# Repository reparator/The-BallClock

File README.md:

# The-BallClock
A minimalistic Clock

If you want to build one or if you are interested in the project, here you can find the parts and instructions:

https://www.thingiverse.com/thing:5811567

https://www.instructables.com/The-BallClock

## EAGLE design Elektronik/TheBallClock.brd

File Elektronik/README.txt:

The BallClock:
Here you find all files related to the electronics hardware: 
Schematics, board, BOM, layouts, assembly diagrams

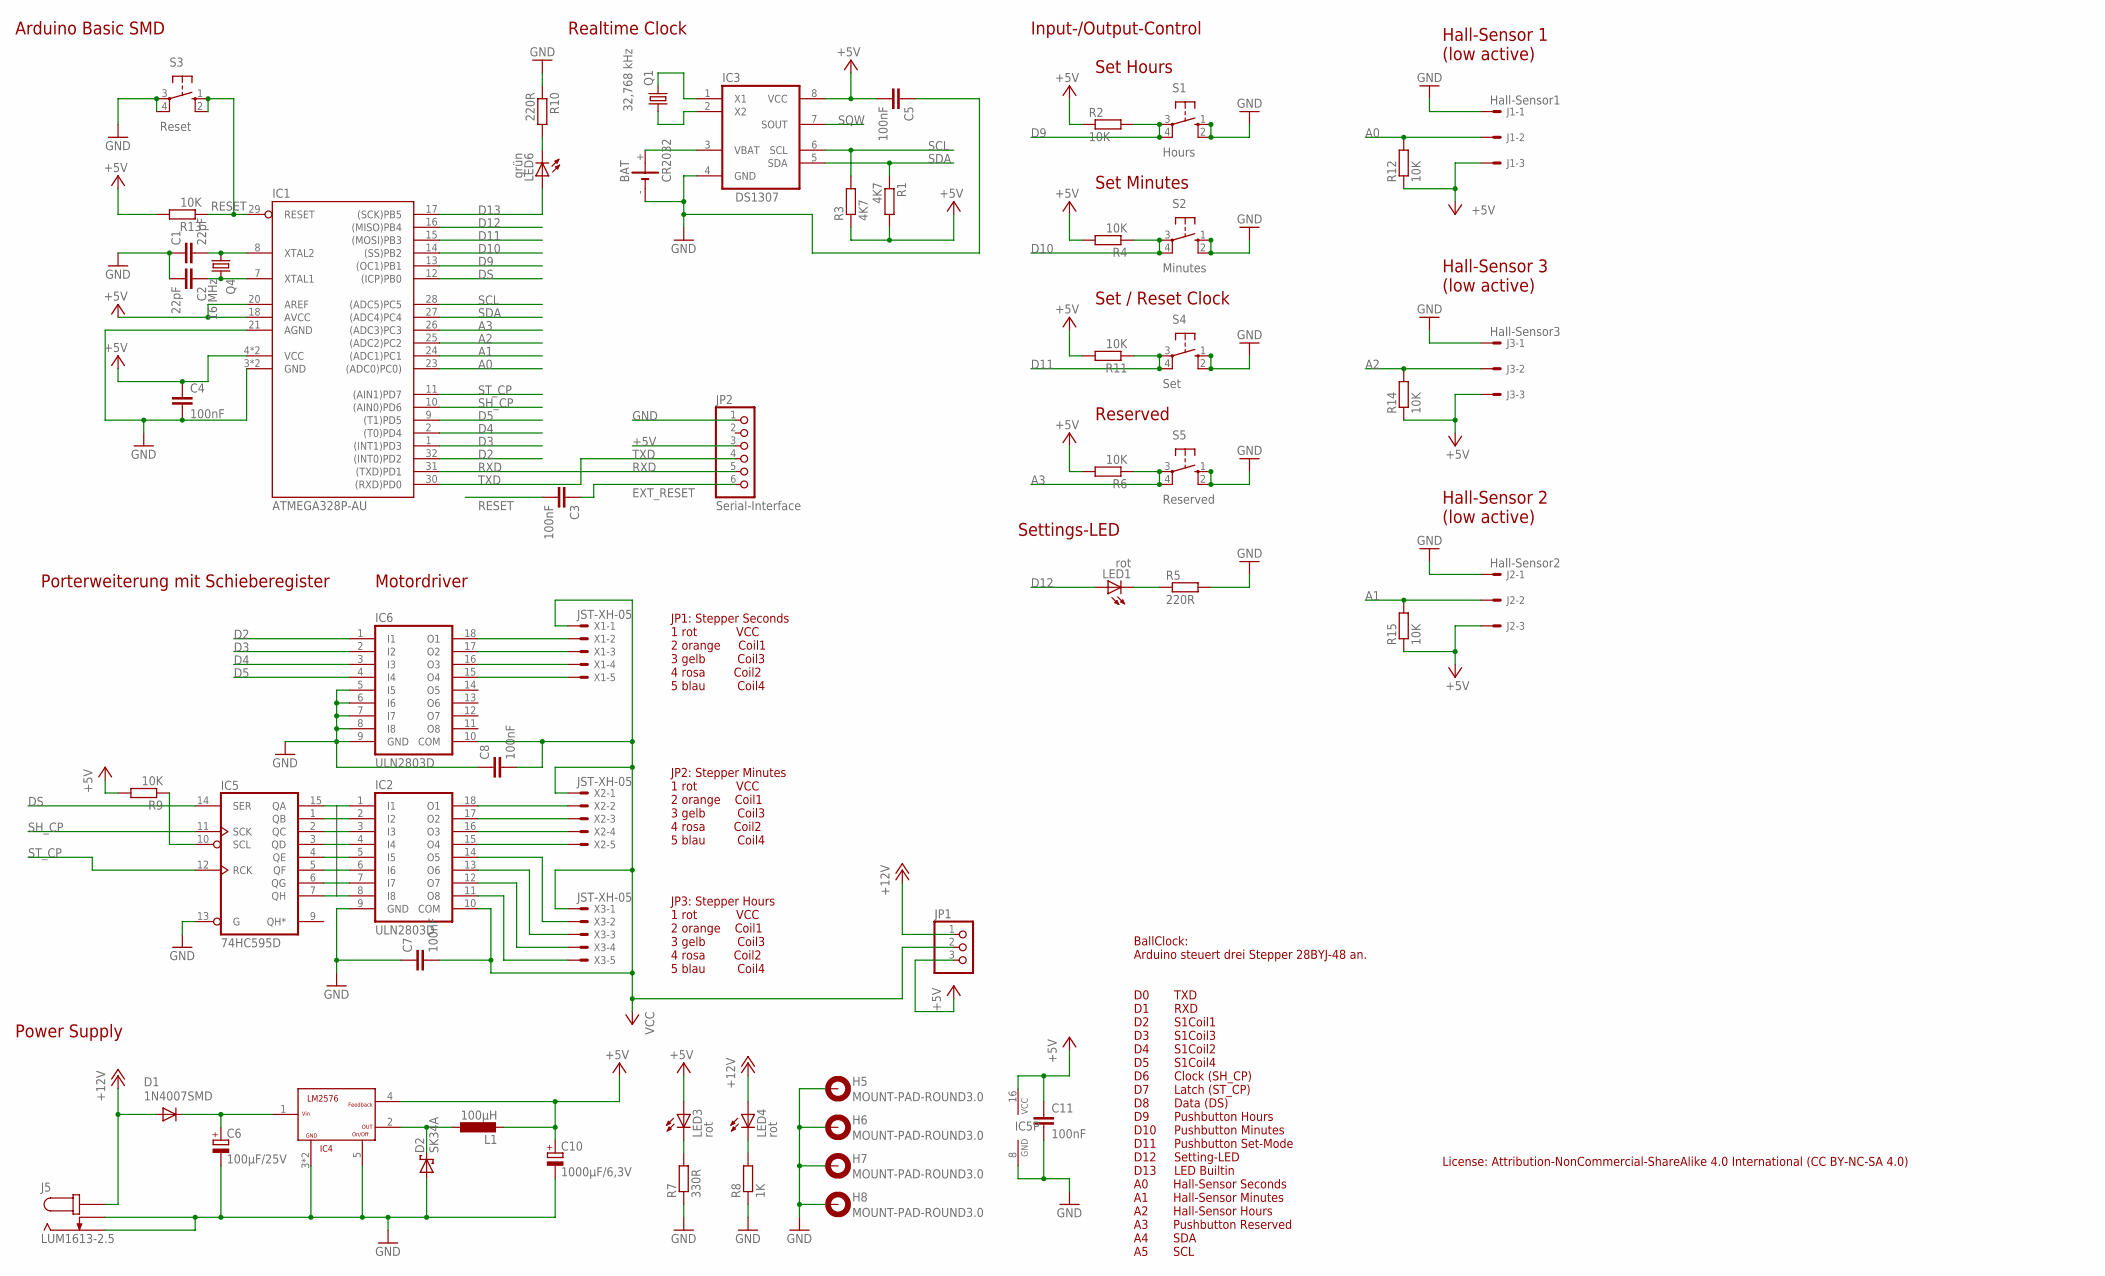
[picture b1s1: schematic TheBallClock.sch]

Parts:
BAT: CR2032; KZH20-SMD
C1, C2: 22pF; C0805K
C3, C4, C5, C7, C8, C11: 100nF; C0805
C6: 100µF/25V; PANASONIC_F
C10: 1000µF/6,3V; PANASONIC_G
D1: 1N4007SMD; SMB
D2: SK34A; DO214AC
H5, H6, H7, H8: MOUNT-PAD-ROUND3.0; 3,0-PAD
IC1: ATMEGA328P-AU; TQFP32-08
IC2, IC6: ULN2803D; SO18W
IC3: DS1307; SO08
IC4: LM2576; TO263-5
IC5: 74HC595D; SO16
J1: Hall-Sensor1; 6410-03
J2: Hall-Sensor2; 6410-03
J3: Hall-Sensor3; 6410-03
J5: LUM1613-2.5; LUM_DS_1613_15
JP1: PINHD-1X3; 1X03
JP2: Serial-Interface; 1X06
L1: 100µH; PISM
LED1, LED3, LED4: rot; CHIPLED_0805
LED6: grün; CHIPLED_0805
Q1: 32,768 kHz; TC38H
Q4: 16 MHz; HC49UP
R1, R3: 4K7; R0805
R2, R4, R6, R11, R12, R13, R14, R15: 10K; M0805
R5, R10: 220R; R0805
R7: 330R; R0805
R8: 1K; R0805
R9: 10K; R0805
S1: Hours; B3F-10XX
S2: Minutes; B3F-10XX
S3: Reset; B3F-10XX
S4: Set; B3F-10XX
S5: Reserved; B3F-10XX
X1, X2, X3: JST-XH-05; JST-XH-05-PACKAGE-LONG-PAD

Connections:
+5V: C4.1, C5.2, C10.+, C11.1, IC1.4 (VCC), IC1.6 (VCC), IC1.18 (AVCC), IC1.20 (AREF), IC3.8 (VCC), IC4.4 (FEEDBACK), IC5.16 (VCC), J1.3, J2.3, J3.3, JP1.3, JP2.3, L1.2, LED3.A, R1.2, R2.1, R3.1, R4.2, R6.2, R9.2, R11.2, R12.1, R13.2, R14.1, R15.1
+12V: D1.A, J5.3A (1), J5.3B (1), JP1.1, LED4.A
A0: IC1.23 ((ADC0)PC0)), J1.2, R12.2
A1: IC1.24 ((ADC1)PC1), J2.2, R15.2
A2: IC1.25 ((ADC2)PC2), J3.2, R14.2
A3: IC1.26 ((ADC3)PC3), R6.1, S5.3, S5.4 (P1)
BUS1: IC2.1 (I1), IC5.15 (QA)
BUS2: IC2.2 (I2), IC5.1 (QB)
BUS3: IC2.3 (I3), IC5.2 (QC)
BUS4: IC2.4 (I4), IC5.3 (QD)
BUS5: IC2.5 (I5), IC5.4 (QE)
BUS6: IC2.6 (I6), IC5.5 (QF)
BUS7: IC2.7 (I7), IC5.6 (QG)
BUS8: IC2.8 (I8), IC5.7 (QH)
D2: IC1.32 ((INT0)PD2), IC6.1 (I1)
D3: IC1.1 ((INT1)PD3), IC6.2 (I2)
D4: IC1.2 ((T0)PD4), IC6.3 (I3)
D5: IC1.9 ((T1)PD5), IC6.4 (I4)
D9: IC1.13 ((OC1)PB1), R2.2, S1.3, S1.4 (P1)
D10: IC1.14 ((SS)PB2), R4.1, S2.3, S2.4 (P1)
D11: IC1.15 ((MOSI)PB3), R11.1, S4.3, S4.4 (P1)
D12: IC1.16 ((MISO)PB4), LED1.A
D13: IC1.17 ((SCK)PB5), LED6.A
DS: IC1.12 ((ICP)PB0), IC5.14 (SER)
EXT_RESET: C3.1, JP2.6
GND: BAT.-, C1.1, C2.2, C4.2, C5.1, C6.-, C7.1, C8.1, C10.-, C11.2, D2.A, H5.B3,0, H6.B3,0, H7.B3,0, H8.B3,0, IC1.3 (GND), IC1.5 (GND), IC1.21 (AGND), IC2.9 (GND), IC3.4 (GND), IC4.3 (GND), IC4.5 (ON/OFF), IC4.6 (GND), IC5.8 (GND), IC5.13 (G), IC6.5 (I5), IC6.6 (I6), IC6.7 (I7), IC6.8 (I8), IC6.9 (GND), J1.1, J2.1, J3.1, J5.1 (2), J5.2 (3), JP2.1, R5.2, R7.1, R8.1, R10.1, S1.1 (S), S1.2 (S1), S2.1 (S), S2.2 (S1), S3.3, S3.4 (P1), S4.1 (S), S4.2 (S1), S5.1 (S), S5.2 (S1)
unnamed: LED1.C, R5.1
unnamed: BAT.+, IC3.3 (VBAT)
unnamed: D2.C, IC4.2 (OUTPUT), L1.1
unnamed: LED3.C, R7.2
unnamed: LED4.C, R8.2
unnamed: C6.+, D1.C, IC4.1 (+VIN)
unnamed: C1.2, IC1.8 (XTAL2), Q4.1
unnamed: IC2.18 (O1), X2.2
unnamed: C2.1, IC1.7 (XTAL1), Q4.2
unnamed: LED6.C, R10.2
unnamed: IC2.17 (O2), X2.3
unnamed: IC2.16 (O3), X2.4
unnamed: IC2.15 (O4), X2.5
unnamed: IC2.14 (O5), X3.2
unnamed: IC2.13 (O6), X3.3
unnamed: IC2.12 (O7), X3.4
unnamed: IC2.11 (O8), X3.5
unnamed: IC6.18 (O1), X1.2
unnamed: IC6.17 (O2), X1.3
unnamed: IC6.16 (O3), X1.4
unnamed: IC6.15 (O4), X1.5
unnamed: IC5.10 (SCL), R9.1
unnamed: IC3.1 (X1), Q1.2
unnamed: IC3.2 (X2), Q1.1
RESET: C3.2, IC1.29 (RESET), R13.1, S3.1 (S), S3.2 (S1)
RXD: IC1.31 ((TXD)PD1), JP2.5
SCL: IC1.28 ((ADC5)PC5), IC3.6 (SCL), R3.2
SDA: IC1.27 ((ADC4)PC4), IC3.5 (SDA), R1.1
SH_CP: IC1.10 ((AIN0)PD6), IC5.11 (SCK)
SQW: IC3.7 (SOUT)
ST_CP: IC1.11 ((AIN1)PD7), IC5.12 (RCK)
TXD: IC1.30 ((RXD)PD0), JP2.4
VCC: C7.2, C8.2, IC2.10 (COM), IC6.10 (COM), JP1.2, X1.1, X2.1, X3.1

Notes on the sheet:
Arduino Basic SMD
Realtime Clock
Input-/Output-Control
Power Supply
Hall-Sensor 1 (low active)
Hall-Sensor 3 (low active)
JP1: Stepper Seconds 1 rot VCC 2 orange Coil1 3 gelb Coil3 4 rosa Coil2 5 blau Coil4
JP2: Stepper Minutes 1 rot VCC 2 orange Coil1 3 gelb Coil3 4 rosa Coil2 5 blau Coil4
BallClock: Arduino steuert drei Stepper 28BYJ-48 an. D0 TXD D1 RXD D2 S1Coil1 D3 S1Coil3 D4 S1Coil2 D5 S1Coil4 D6 Clock (SH_CP) D7 Latch (ST_CP) D8 Data (DS) D9 Pushbutton Hours D10 Pushbutton Minutes D11 Pushbutton Set-Mode D12 Setting-LED D13 LED Builtin A0 Hall-Sensor Seconds A1 Hall-Sensor Minu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
Porterweiterung mit Schieberegister
Motordriver
Hall-Sensor 2 (low active)
JP3: Stepper Hours 1 rot VCC 2 orange Coil1 3 gelb Coil3 4 rosa Coil2 5 blau Coil4
Set Hours
Set Minutes
Set / Reset Clock
Settings-LED
Reserved
License: Attribution-NonCommercial-ShareAlike 4.0 International (CC BY-NC-SA 4.0)

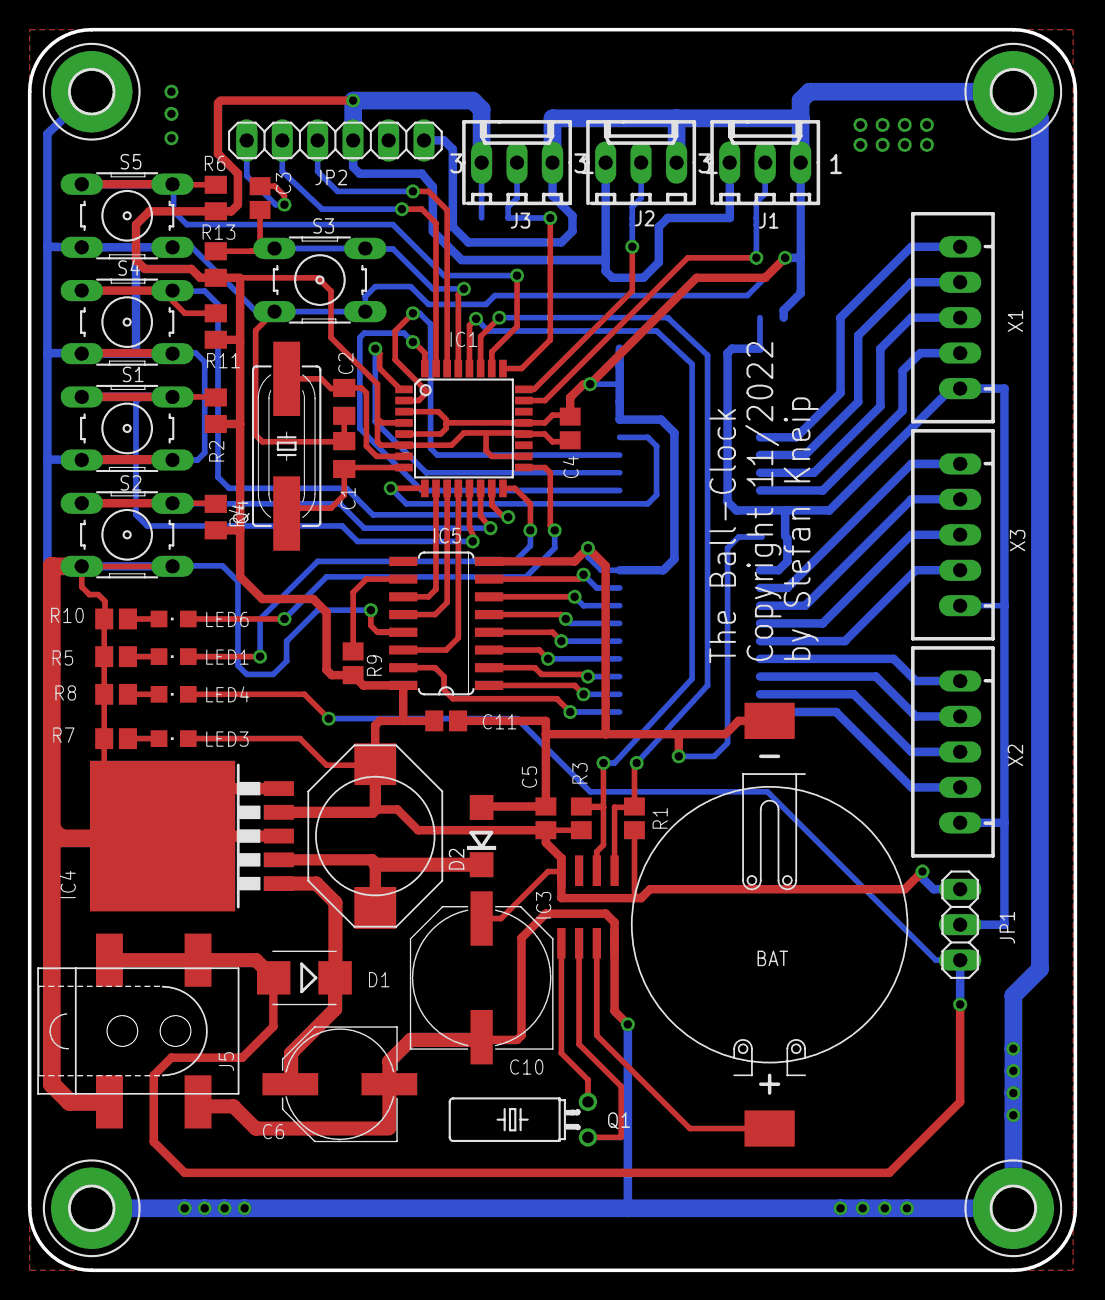
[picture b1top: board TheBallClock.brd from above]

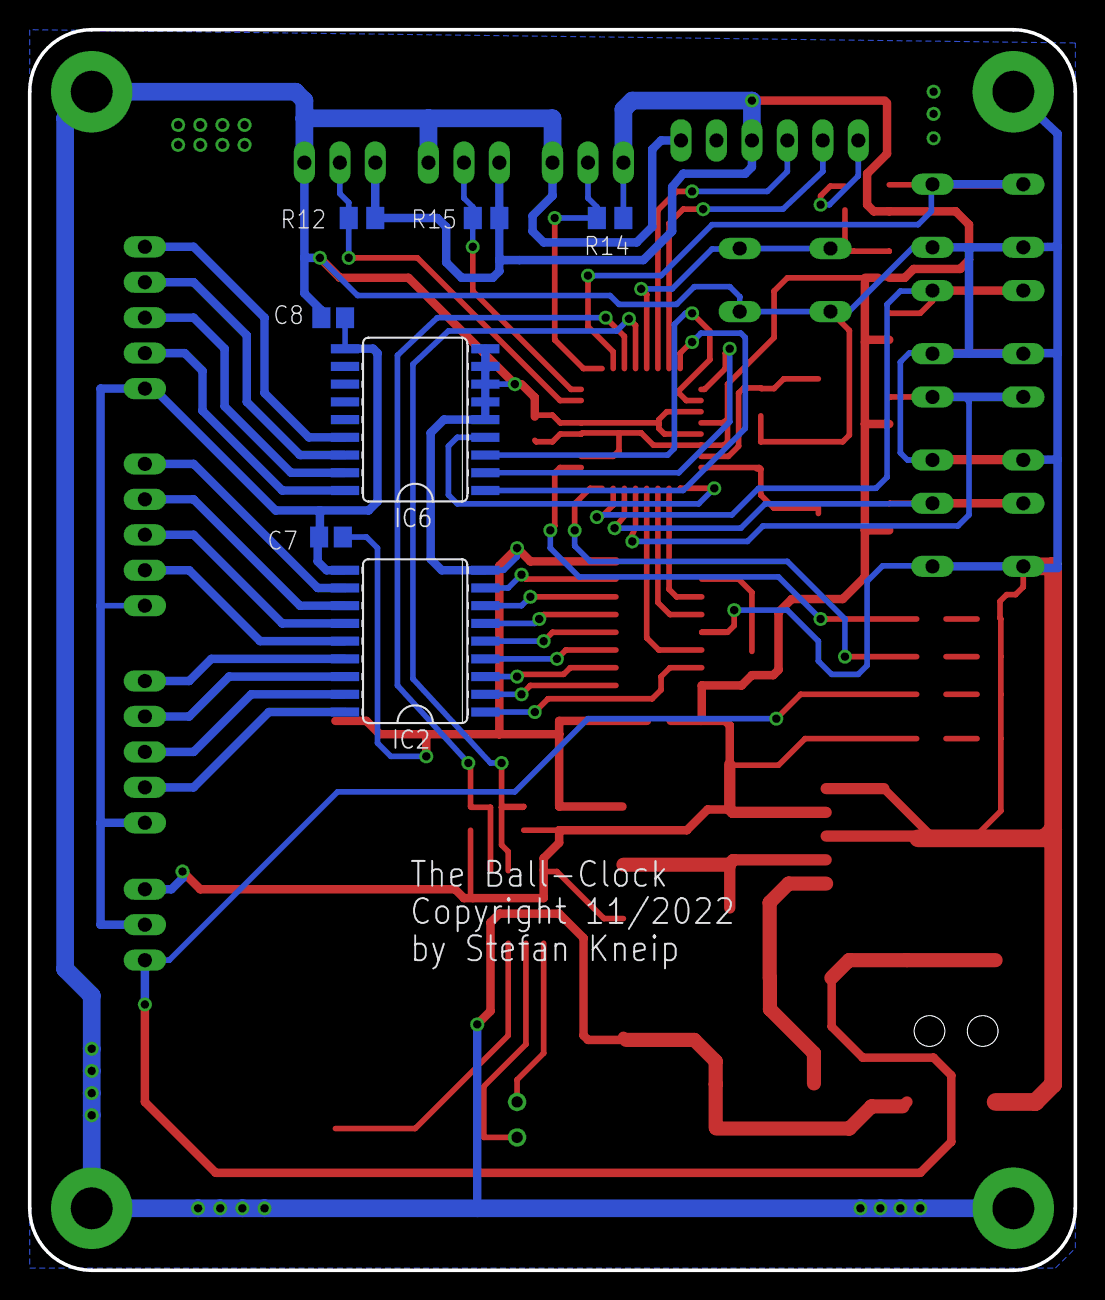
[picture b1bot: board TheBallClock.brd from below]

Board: 2 copper layers, 74.9 x 88.9 mm, 59 parts (7 on the bottom side), 58 nets.

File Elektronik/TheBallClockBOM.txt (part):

Stückliste exportiert am 09.01.2023 12:06:00

Part Value              Device                 Package                    Description                          MF MPN      OC_FARNELL OC_NEWARK
BAT  CR2032             BATTERIEHALTER_KZH20   KZH20-SMD                  KZH 20                                                               
C1   22pF               C-EUC0805K             C0805K                     CAPACITOR, European symbol                                           
C2   22pF               C-EUC0805K             C0805K                     CAPACITOR, European symbol                                           
C3   100nF              C-EUC0805              C0805                      CAPACITOR, European symbol                                           
C4   100nF              C-EUC0805              C0805                      CAPACITOR, European symbol                                           
C5   100nF              C-EUC0805              C0805                      CAPACITOR, European symbol                                           
C6   100µF/25V          CPOL-EUF               PANASONIC_F                POLARIZED CAPACITOR, European symbol                                 
C7   100nF              C-EUC0805              C0805                      CAPACITOR, European symbol                                           
C8   100nF              C-EUC0805              C0805                      CAPACITOR, European symbol                                           
C10  1000µF/6,3V        CPOL-EUG               PANASONIC_G                POLARIZED CAPACITOR, European symbol                                 
C11  100nF              C-EUC0805              C0805                      CAPACITOR, European symbol                                           
D1   1N4007SMD          DIODE-SMB              SMB                        DIODE                                                                
D2   SK34A              SK34A                  DO214AC                                                                                         
H5   MOUNT-PAD-ROUND3.0 MOUNT-PAD-ROUND3.0     3,0-PAD                    MOUNTING PAD, round                                                  
H6   MOUNT-PAD-ROUND3.0 MOUNT-PAD-ROUND3.0     3,0-PAD                    MOUNTING PAD, round                                                  
H7   MOUNT-PAD-ROUND3.0 MOUNT-PAD-ROUND3.0     3,0-PAD                    MOUNTING PAD, round                                                  
H8   MOUNT-PAD-ROUND3.0 MOUNT-PAD-ROUND3.0     3,0-PAD                    MOUNTING PAD, round                                                  
IC1  ATMEGA328P-AU      ATMEGA328P-AU          TQFP32-08                  MICROCONTROLLER                                                      
IC2  ULN2803D           ULN2803D               SO18W                      ULN2803 Darlington Arrays                                            
IC3  DS1307             DS1307Z                SO08                       DS1307                                                               
IC4  LM2576             LM2576                 TO263-5                    LM2576                                                               
IC5  74HC595D           74HC595D               SO16                       8-bit SHIFT REGISTER, output latch                                   
IC6  ULN2803D           ULN2803D               SO18W                      ULN2803 Darlington Arrays                                            
J1   Hall-Sensor1       22-27-2031-03          6410-03                    CONNECTOR                                                            
J2   Hall-Sensor2       22-27-2031-03          6410-03                    CONNECTOR                                                            
J3   Hall-Sensor3       22-27-2031-03          6410-03                    CONNECTOR                                                            
J5   LUM1613-2.5        LUM1613-2.5            LUM_DS_1613_15             Lumberg 1613                                                         
JP1                     PINHD-1X3              1X03                       PIN HEADER                                                           
JP2  Serial-Interface   PINHD-1X6              1X06                       PIN HEADER                                                           
L1   100µH              L-EUPISM               PISM                                                                                            
LED1 rot                LEDCHIPLED_0805        CHIPLED_0805               LED                                                                  
LED3 rot                LEDCHIPLED_0805        CHIPLED_0805               LED                                                                  
LED4 rot                LEDCHIPLED_0805        CHIPLED_0805               LED                                                                  
LED6 grün               LEDCHIPLED_0805        CHIPLED_0805               LED                                                                  
Q1   32,768 kHz         CRYSTALTC38H           TC38H                      CRYSTAL                                          unknown    unknown  
Q4   16 MHz             CRYSTALHC49UP          HC49UP                     CRYSTAL                                          unknown    unknown  
R1   4K7                R-EU_R0805             R0805                      RESISTOR, European symbol                                            
R2   10K                R-EU_M0805             M0805                      RESISTOR, European symbol                                            
R3   4K7                R-EU_R0805             R0805                      RESISTOR, European symbol                                            
R4   10K                R-EU_M0805             M0805                      RESISTOR, European symbol                                            
R5   220R               R-EU_R0805             R0805                      RESISTOR, European symbol                                            
R6   10K                R-EU_M0805             M0805                      RESISTOR, European symbol                                            
R7   330R               R-EU_R0805             R0805                      RESISTOR, European symbol                                            
R8   1K                 R-EU_R0805             R0805                      RESISTOR, European symbol                                            
R9   10K                R-EU_R0805             R0805                      RESISTOR, European symbol                                            
R10  220R               R-EU_R0805             R0805                      RESISTOR, European symbol                                            
R11  10K                R-EU_M0805             M0805                      RESISTOR, European symbol                                            
R12  10K                R-EU_M0805             M0805                      RESISTOR, European symbol                                            
R13  10K                R-EU_M0805             M0805                      RESISTOR, European symbol                                            
R14  10K                R-EU_M0805             M0805                      RESISTOR, European symbol                                            
R15  10K                R-EU_M0805             M0805                      RESISTOR, European symbol                                            
S1   Hours              10-XX                  B3F-10XX                   OMRON SWITCH                            B3F-1000 176432     36M3542  
S2   Minutes            10-XX                  B3F-10XX                   OMRON SWITCH                            B3F-1000 176432     36M3542  
S3   Reset              10-XX                  B3F-10XX                   OMRON SWITCH                            B3F-1000 176432     36M3542  
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

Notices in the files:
parts and their libraries:
MyEagle: CC Copyright by Stefan Kneip
